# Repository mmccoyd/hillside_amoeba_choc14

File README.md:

# Hillside Amoeba Choc14

|                 |                 |
|:-----------     |:----------------|
|  |  |

These are single-switch PCBs for Choc spaced Dactyl keyboards.

They allow Choc 18 mm or narrower column spacing,
  sturdier column walls, and Mill-Max hot swap.
Each has a PCBA SOD-123 diode, holes for a Choc v1 switch with optional
    Mill-Max sockets, and wire solder holes for creating the switch matrix.
The diode is from column anode+ to row cathode-.

Goals include
  allowing most of the matrix soldering to be done outside of the case
  and allowing reuse of the switches and matrix in a future case.

See the [wiki](https://github.com/mmccoyd/hillside_amoeba_choc14/wiki)
    for ordering details and wiring suggestions.
Their use is illustrated in the
    [Hillside Dactyl 50](https://github.com/mmccoyd/hillside_dactyl_50)
    wiki.

## Size and fit

The PCBs are 13.7 wide x 16 mm deep.

That is only as wide as the bottom of a choc switch,
  but adds a small top and bottom lip
  to prevent removal of the switch from pulling the PCB out of the key well.
Side notches serve to keep the top to bottom position aligned
  with the keyboard-body's switch-socket hole and to
  prevent the PCB from falling into the switch hole.

## Panel layout

The fabrication panel spacing matches that seen in a typical Dactyl key well.
That simplifies building by allowing much of the wiring to be done
  before splitting the PCBs out of the panel.

The column separation in the panel
  has a bit of slack for the intervening key well wall.
This mirrors what is likely needed in the key well 
  for the usually parallel pinkie and index columns.
The panel separation of 20 mm adds 2 mm to the choc 18 mm column separation.

The row edge-to-edge separation
    leaves a decent tab between the PCBs
    to grip with pliers to break the PCBs cleanly apart.
The separation of 6 mm adds 2 mm to the key well 3.8 mm separation
  for a column of 16 mm PCBs with a 15 degree curve.

## Version status

-   Alpha.4: Net yet tested. Has the larger SOD-123 diodes for hand soldering.
-   Alpha.3: Used without PCBA by A SadWitch. Has the small SOD-323 diodes.
-   Alpha.2: I used with PCBA for my Hillside Dactyl 50 alpha.2 and alpha.3.

## Images

Images of use in a build are in the
    [Hillside Dactyl 50](https://github.com/mmccoyd/hillside_dactyl_50) wiki.

## Other Choc Amoeba options

There are a few other choc Amoebas, though they have wider footprints:

- [Amoeba-choc](https://github.com/girishji/amoeba-choc)
  with monochrome LED and lower power draw, plus Kailh hotswap.
- [Nydas Amoeba](https://github.com/nydasco/nydas_keyboard_v2/tree/main/NydasAmoeba)
  with SK6812-mini-e LED and Kailh hotswap.
- [MxLEDBit](https://keycapsss.com/keyboard-parts/pcbs/173/mxledbit-single-switch-pcb-mx-choc-hot-swap-socket)
  with SK6812-mini-e LED and no hotswap.
- [Skree](https://www.skree.us) has MX spaced amoebas that also take choc switches.
- [su120](https://github.com/kissetfall/su120-keyboard/tree/master)

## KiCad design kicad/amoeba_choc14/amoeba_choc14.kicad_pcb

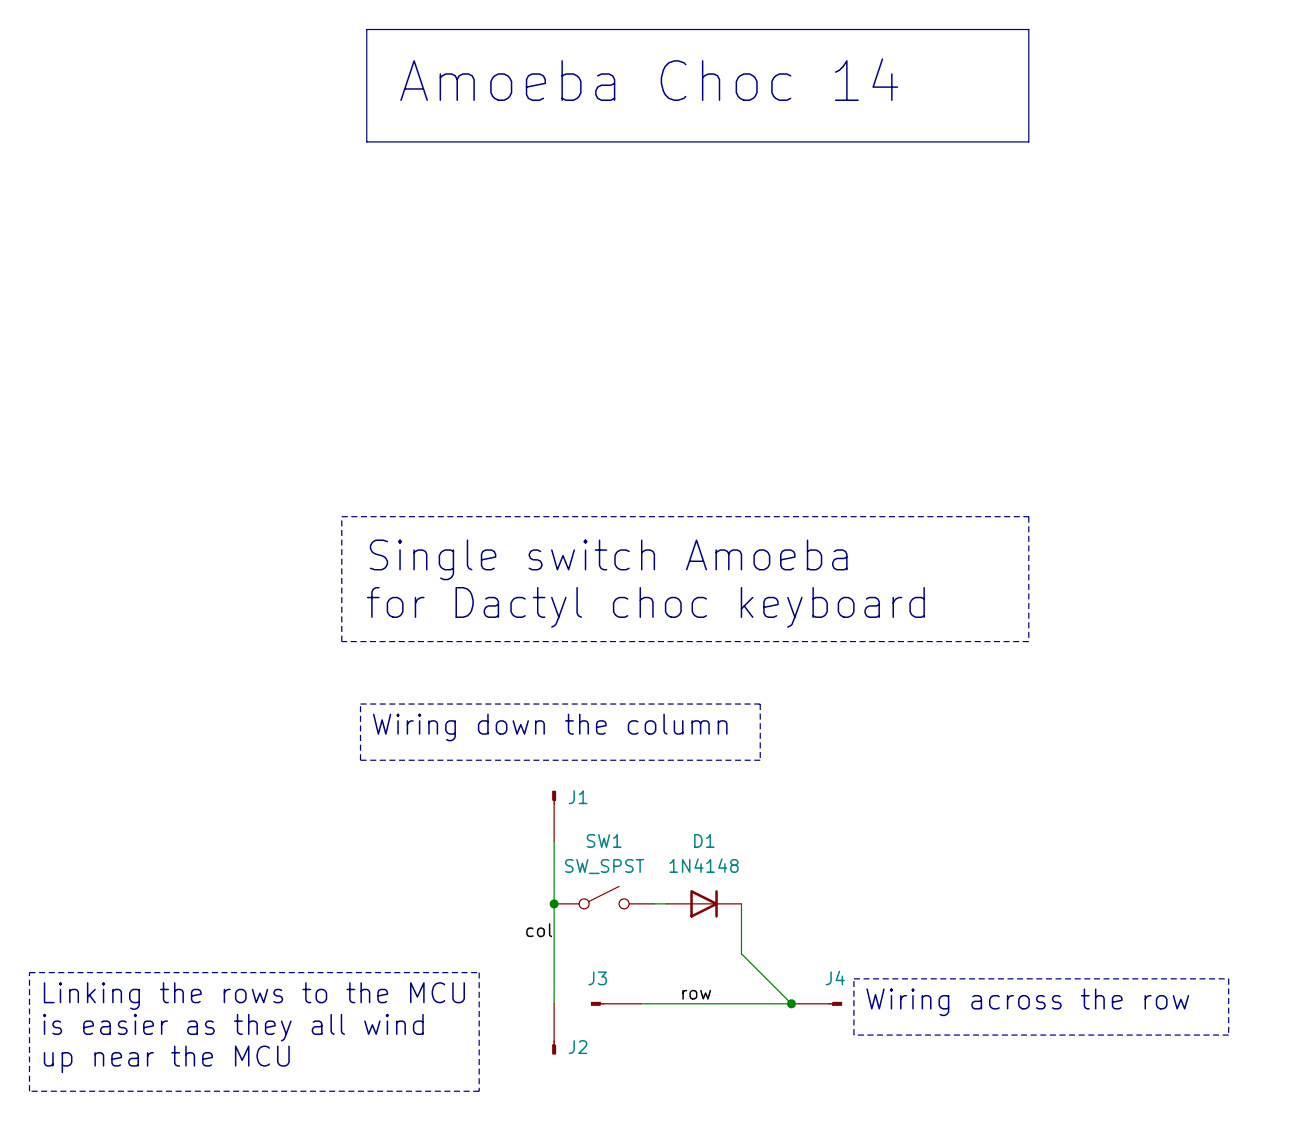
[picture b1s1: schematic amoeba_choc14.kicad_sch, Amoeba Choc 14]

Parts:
D1: 1N4148; D_SOD-123; LCSC C81598
J1, J2, J3, J4: Conn_01x01_Pin; Pin_D0.8mm_L7.0mm
SW1: SW_SPST; pg1350-hotswap

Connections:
/col: J1.1, J2.1, SW1.1 (A)
/row: D1.1 (K), J3.1, J4.1
unnamed: D1.2 (A), SW1.2 (B)

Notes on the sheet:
${TITLE}
Linking the rows to the MCU is easier as they all wind up near the MCU
Single switch Amoeba for Dactyl choc keyboard
Wiring down the column
Wiring across the row

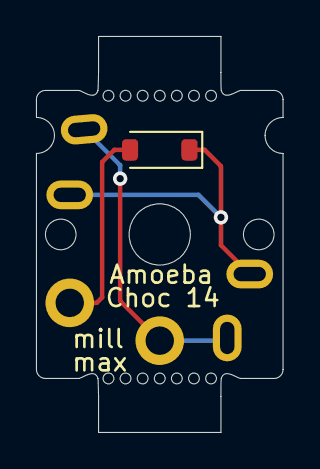
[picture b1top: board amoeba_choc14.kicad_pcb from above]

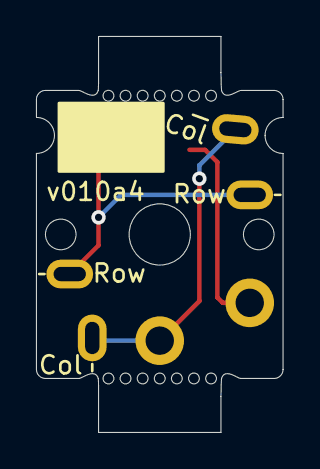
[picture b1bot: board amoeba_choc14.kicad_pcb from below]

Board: 2 copper layers, 13.7 x 22.0 mm, 6 parts (4 on the bottom side), 3 nets.

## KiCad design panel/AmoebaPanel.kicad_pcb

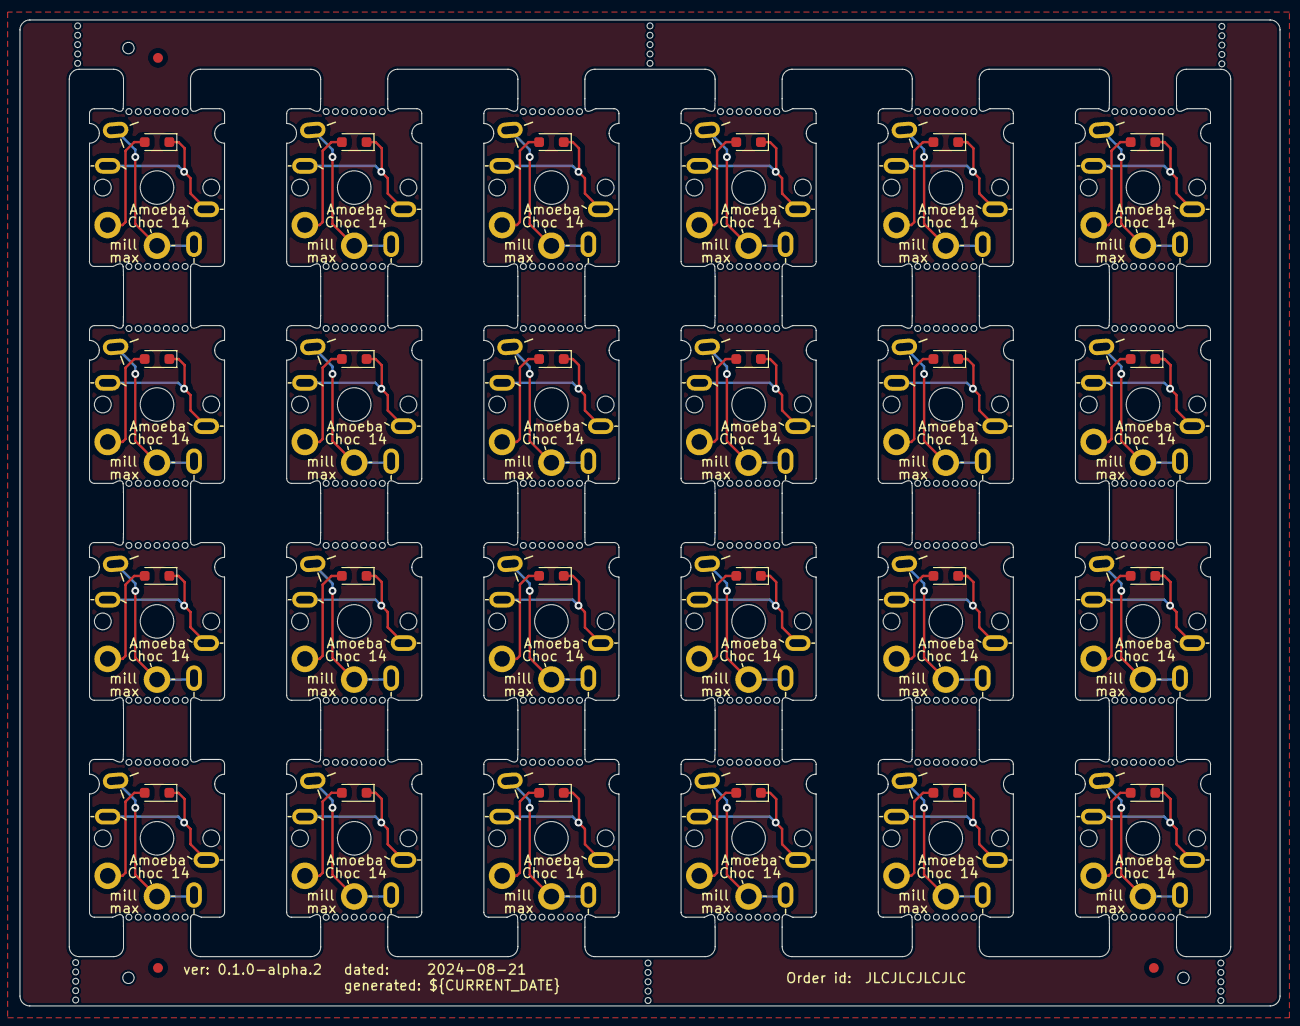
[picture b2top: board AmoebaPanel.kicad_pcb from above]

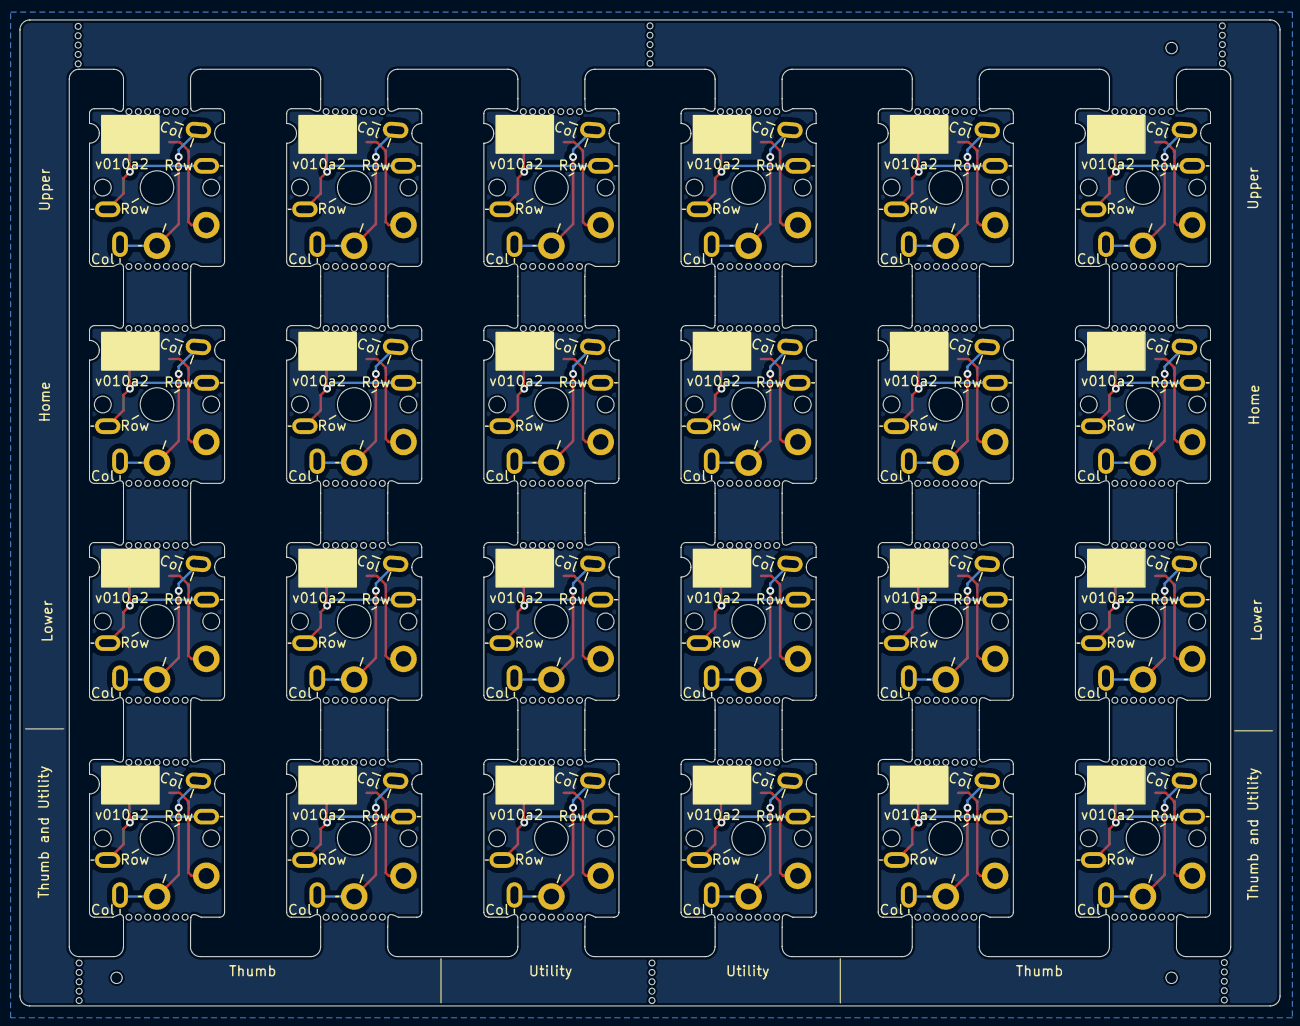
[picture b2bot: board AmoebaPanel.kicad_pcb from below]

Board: 2 copper layers, 127.8 x 100.0 mm, 144 parts (96 on the bottom side), 3 nets.

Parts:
D1, D1#2, D2, D3, D4, D5, D6, D7, D8, D9, D10, D11, D12, D13, D14, D15, D16, D17, D18, D19, D20, D21, D22, D23: 1N4148; D_SOD-323_HandSoldering
J1, J1#2, J2, J2#2, J3, J3#2, J4, J4#2, J5, J6, J7, J8, J9, J10, J11, J12, J13, J14, J15, J16, J17, J18, J19, J20, J21, J22, J23, J24, J25, J26, J27, J28, J29, J30, J31, J32, J33, J34, J35, J36, J37, J38, J39, J40, J41, J42, J43, J44, J45, J46, J47, J48, J49, J50, J51, J52, J53, J54, J55, J56, J57, J58, J59, J60, J61, J62, J63, J64, J65, J66, J67, J68, J69, J70, J71, J72, J73, J74, J75, J76, J77, J78, J79, J80, J81, J82, J83, J84, J85, J86, J87, J88, J89, J90, J91, J92: Conn_01x01_Pin; Pin_D0.8mm_L7.0mm
SW1, SW1#2, SW2, SW3, SW4, SW5, SW6, SW7, SW8, SW9, SW10, SW11, SW12, SW13, SW14, SW15, SW16, SW17, SW18, SW19, SW20, SW21, SW22, SW23: SW_SPST; pg1350-hotswap

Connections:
/col: J1.1, J1#2.1, J2.1, J2#2.1, J5.1, J6.1, J9.1, J10.1, J13.1, J14.1, J17.1, J18.1, J21.1, J22.1, J23.1, J24.1, J29.1, J30.1, J33.1, J34.1, J37.1, J38.1, J41.1, J42.1, J45.1, J46.1, J47.1, J48.1, J53.1, J54.1, J57.1, J58.1, J61.1, J62.1, J65.1, J66.1, J69.1, J70.1, J71.1, J72.1, J77.1, J78.1, J81.1, J82.1, J85.1, J86.1, J89.1, J90.1, SW1.1 (A), SW1#2.1 (A), SW2.1 (A), SW3.1 (A), SW4.1 (A), SW5.1 (A), SW6.1 (A), SW7.1 (A), SW8.1 (A), SW9.1 (A), SW10.1 (A), SW11.1 (A), SW12.1 (A), SW13.1 (A), SW14.1 (A), SW15.1 (A), SW16.1 (A), SW17.1 (A), SW18.1 (A), SW19.1 (A), SW20.1 (A), SW21.1 (A), SW22.1 (A), SW23.1 (A)
/row: D1.1 (K), D1#2.1 (K), D2.1 (K), D3.1 (K), D4.1 (K), D5.1 (K), D6.1 (K), D7.1 (K), D8.1 (K), D9.1 (K), D10.1 (K), D11.1 (K), D12.1 (K), D13.1 (K), D14.1 (K), D15.1 (K), D16.1 (K), D17.1 (K), D18.1 (K), D19.1 (K), D20.1 (K), D21.1 (K), D22.1 (K), D23.1 (K), J3.1, J3#2.1, J4.1, J4#2.1, J7.1, J8.1, J11.1, J12.1, J15.1, J16.1, J19.1, J20.1, J25.1, J26.1, J27.1, J28.1, J31.1, J32.1, J35.1, J36.1, J39.1, J40.1, J43.1, J44.1, J49.1, J50.1, J51.1, J52.1, J55.1, J56.1, J59.1, J60.1, J63.1, J64.1, J67.1, J68.1, J73.1, J74.1, J75.1, J76.1, J79.1, J80.1, J83.1, J84.1, J87.1, J88.1, J91.1, J92.1
unnamed: D1.2 (A), D1#2.2 (A), D2.2 (A), D3.2 (A), D4.2 (A), D5.2 (A), D6.2 (A), D7.2 (A), D8.2 (A), D9.2 (A), D10.2 (A), D11.2 (A), D12.2 (A), D13.2 (A), D14.2 (A), D15.2 (A), D16.2 (A), D17.2 (A), D18.2 (A), D19.2 (A), D20.2 (A), D21.2 (A), D22.2 (A), D23.2 (A), SW1.2 (B), SW1#2.2 (B), SW2.2 (B), SW3.2 (B), SW4.2 (B), SW5.2 (B), SW6.2 (B), SW7.2 (B), SW8.2 (B), SW9.2 (B), SW10.2 (B), SW11.2 (B), SW12.2 (B), SW13.2 (B), SW14.2 (B), SW15.2 (B), SW16.2 (B), SW17.2 (B), SW18.2 (B), SW19.2 (B), SW20.2 (B), SW21.2 (B), SW22.2 (B), SW23.2 (B)

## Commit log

2024-02-21 doc: initial readme with blurb
2024-04-11 feat: empty KiCad project
2024-04-11 feat(amoeba): clean up, hold just amoeba area
2024-04-11 feat(PCBA): add LCSC number for diode
2024-04-11 feat: POS exclude in pcb
2024-04-11 feat(panel): 4x5 panel, mouse bites, silk versions
2024-04-11 fix: label vs mask, update dioode from lib
2024-04-11 feat(CI): BOM only smd
2024-04-11 feat(foot): tooling hole
2024-04-11 refactor(CI): update for folder changes
2024-04-11 feat(foot): mouse bites just hole no larger mask
2024-04-11 chore: gitignore: lock, cache
2024-04-11 feat: Config "do not fit"
2024-04-11 feat(CI): use explicit dnf filter
2024-04-11 refactor: rename v2
2024-04-11 feat(debug): PCBA SMD only
2024-04-11 feat(CI): debug exclude marked in schema
2024-04-11 feat: extrude from BOM and position file
2024-04-11 feat(foot): switch: show hole and choc space size
2024-04-11 feat(CI): debug exclude marked in pcb
2024-04-11 feat(debug): PCBA not separate files
2024-04-11 feat(foot): diode on front
2024-04-11 feat: project sheet description; KiCad defaults
2024-04-11 feat: update PCB footprint
2024-04-11 feat: project clearance update from kicad
2024-04-11 feat(foot): choc switch
2024-04-11 feat(amoeba): cleanup
2024-04-11 feat(PCBA): rough copy of KiBot from hillside
2024-04-11 feat(CI): debug BOM ignore_dnf
2024-04-11 feat(schematic): exclude switch from BOM
2024-04-11 feat(foot): extrude from BOM and position file
2024-04-11 feat(foot): mouse bits
2024-04-11 feat(CI): call for KiBot k8
2024-04-11 feat(foot): 1 pin connector
2024-04-11 feat(CI): debug no BOM
2024-04-11 chore: git ignore of renamed files
2024-04-11 refactor: rename v3
2024-04-11 feat(debug): PCBA simplify options
2024-04-11 refactor: kicad precision cleanup
2024-04-11 feat: choc, diode, connectors, silk. rename folder
2024-04-11 chore: gitignore: backups
2024-04-11 refactor: rename folders to amoeba/ and panel/
2024-04-11 feat(debug): disable KiBot BOM
2024-04-11 feat(CI): use default dnf filter
2024-04-11 feat(CI): BOM
2024-04-11 feat: create footprint library
2024-04-11 feat(amoeba): extra column pad for MCU connection
2024-04-11 feat(sch): Title block info
2024-04-11 feat(panel): 5 x 5 grid, docs
2024-05-01 feat(foot): width 13.7 mm
2024-05-01 feat: width 13.7 mm, clearer row/col silk
2024-05-01 feat(panel): update for width 13.7mm
2024-05-01 doc: cleanup readme. Ordering, design, wiring.
2024-05-14 feat(foot): mouse bites for panel rails
2024-05-14 feat(panel): mouse bites on rails, fix lib path
2024-05-14 doc: tidy up readme
2024-05-14 feat(panel): longer bite tabs for breakoff
2024-05-14 feat: longer bite tabs for breakoff; mini ver num
2024-05-15 feat: use SOD-323 diode, as 123 out of stock
2024-05-15 feat(foot): fix tooling hole must be unplated
2024-05-15 feat(pcb): update for SOD-323
2024-05-15 feat(panel): update for SOD-323
2024-05-15 doc: note diode options if out of stock
2024-05-24 feat(panel): tidy up tooling holes and silk
2024-06-01 feat(foot): choc: use labels not box for mill max
2024-06-01 feat(foot): wire solder hole: oval shape
2024-06-01 feat: oval wire pads offset for easier curve
2024-06-01 feat(panel): label rows and thumbs on edge rails
2024-08-21 feat(foot): pg1350 more room at top for mouse bite
2024-08-23 feat(panel): space out to match wiring distances
2024-08-23 feat(pcb): use slots for wire holes. better bites
    - Row and col are slots to more easily cram wire into them.
    - No extra lower column pad
    - Better separation between upper col and row
    - Mouse bites recessed so broken edge should lie inside the board outline.
2024-08-23 feat(step): update export
2024-08-23 feat(panel): panel shows a sample wiring layoout
2024-08-23 doc: cleanup ordering, expand readme
2024-08-23 refactor: move kicad into own dir kicad/
2024-08-23 refactor: move kicad into own directory
2025-01-15 doc: readme, wiki, and Changlog updates
2025-03-23 doc(wiki): move wiki into separate repo
2025-03-23 doc: changelog and status cleanups
2025-04-17 ci: remove ci as using KiCad JLC build plugin
2025-04-17 feat(panel): re-insert Amoeba
2025-04-17 feat(amoeba): bump version, straighten trace
    - update to KiCad 9
    - increase font size in schematic
2025-04-17 feat(KiCad): update to KiCad 9
2025-04-17 feat(panel): better wording, move tooling holes
2025-04-17 feat(JLC plugin): update JLC fabrication plugin
2025-04-17 feat: License
2025-04-17 feat(panel): silk wording tweaks
2025-04-17 ci: release build kicad file churn..
2025-04-17 chore: update panel release date
2025-04-17 doc: change log and readme
2025-06-10 doc: tidy up writing, update for Hillside release
2025-06-28 feat(panel): fix silk typo, add art, bump version
2025-06-28 feat(amoeba): SOD-123 diode, fewer silk tick marks
2025-06-28 feat(panel): updated amoeba
2025-06-28 feat(panel): exclude logo from parts lists
2025-06-29 doc: readme and changelog for alpha.4
